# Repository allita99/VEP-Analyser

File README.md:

# VEP-Analyser-Motherboard

This repository contains an updated version of the hardware and software developed during my Bachelor's thesis, with incremental improvements and ongoing refinements.

The project integrates multiple components required for a VEP-based system, including firmware, sensor hardware, and the main motherboard design.

---

## Contents

* **Microcontroller Code**
  Firmware used for signal acquisition, control, and system interaction.

* **Motherboard Design**
  Central hardware platform responsible for system integration, power distribution, and communication between components.

* **VEP Sensor (VEPsor) Design**
  Hardware for acquiring visual evoked potential signals.

---

## Status

This repository reflects a working but evolving system:

* Several design and implementation improvements have been applied compared to the original thesis version
* Some components are still under development or require further validation
* Minor inconsistencies or unfinished elements may remain

---

## Purpose

The project is intended for:

* Research and experimentation in Brain-Computer Interfaces (BCI)
* Development and testing of VEP-based acquisition systems
* Educational use and hardware/software prototyping

---

## Notes

* Hardware designs may require verification before fabrication
* Firmware may need adaptation depending on the specific setup
* Some features are still work in progress and subject to change

---

Acknowledgement

Parts of the documentation and written content in this repository were generated with the assistance of AI tools. The text may be revised in the future if inaccuracies, inconsistencies, or improvements are identified.

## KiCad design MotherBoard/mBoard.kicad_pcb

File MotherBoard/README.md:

# VEPsor – Motherboard Hardware

The **VEPsor Motherboard** is the central hardware component of the VEP Analyzer project. It functions as the primary interface between VEP sensor modules, processing units, and external systems, enabling reliable data acquisition and seamless system integration.

This repository contains all resources required to review, manufacture, and assemble the motherboard.

---

## Preview

---

## Repository Contents

- **KiCad Project Files**  
  Complete schematic and PCB layout files for modification and extension.

- **Bill of Materials (BOM)**  
  Comprehensive list of components required for assembly.

- **Gerber Files**  
  Manufacturing-ready files for PCB fabrication.

- **schematics.pdf**  
  Exported schematic for quick inspection of the circuit design.

---

## Overview

The motherboard is designed to:

- Interface with VEP sensor modules  
- Provide stable power distribution across the system  
- Enable communication between hardware components  
- Serve as a reliable platform for BCI system integration  

### Key Design Goals

- Modular integration with sensor units  
- Robust signal routing and power management  
- Use of standard, widely available components  
- Expandability for future system extensions  

---

## Getting Started

### 1. Review the Design
- Open the KiCad project files for full access to the design  
- Use `schematics.pdf` for a quick overview  

### 2. PCB Fabrication
- Upload the Gerber files to a PCB manufacturer (e.g., JLCPCB, PCBWay)

### 3. Component Sourcing
- Use the BOM to procure all required components  

### 4. Assembly
- Assemble the board according to the PCB layout and schematic  
- Verify all power rails and connections before powering the system  

---

## Notes

- Ensure proper handling of power distribution sections  
- Follow ESD safety procedures during assembly  
- Validate voltage levels before connecting sensor modules  

---

## Intended Use

This hardware is intended for:

- Research and development in BCI systems  
- Integration of VEP-based sensing platforms  
- Experimental signal acquisition and processing setups  

This system is **not intended for medical or clinical use**.

---

## Feedback and Contributions

Feedback is encouraged. If you identify a bug, design issue, documentation error, or have suggestions for improvement, please open an Issue.

Constructive comments and contributions are welcome.

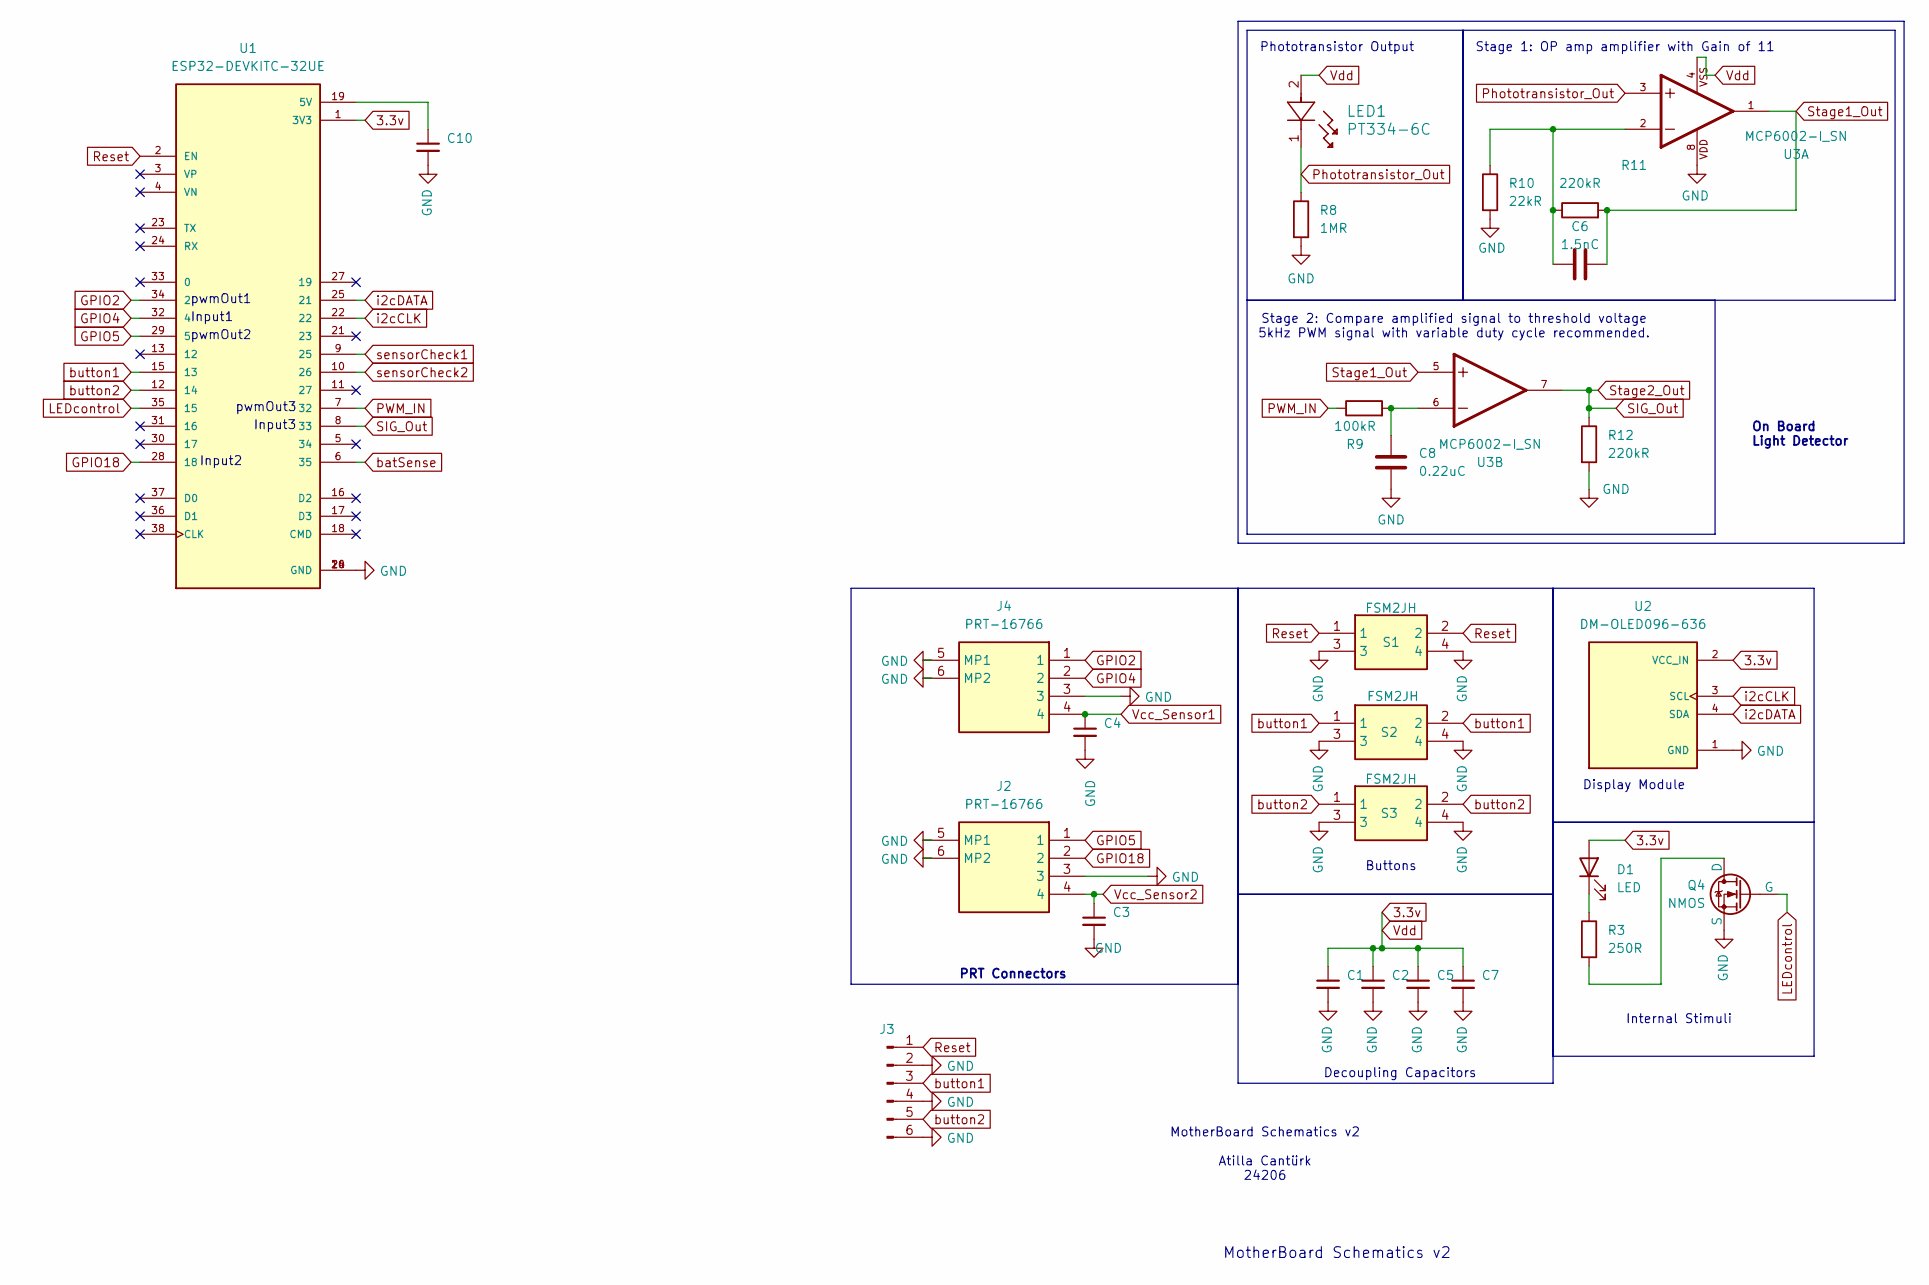
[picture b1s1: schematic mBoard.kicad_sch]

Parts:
C1, C2, C3, C4, C5, C7, C10: C_Small; C_1206_3216Metric_Pad1.33x1.80mm_HandSolder
C6: 1.5nC; C_1206_3216Metric_Pad1.33x1.80mm_HandSolder
C8: 0.22uC; C_1206_3216Metric_Pad1.33x1.80mm_HandSolder
D1: LED; LED_D5.0mm
J2, J4: PRT-16766; PRT16766; Mouser Part Number 474-PRT-16766
J3: Conn_01x06_Pin; PinHeader_1x06_P2.54mm_Vertical
LED1: PT334-6C; LED_D5.0mm
Q4: NMOS; SOT-23_Handsoldering
R3: 250R; R_1206_3216Metric_Pad1.30x1.75mm_HandSolder
R8: 1MR; R_1206_3216Metric_Pad1.30x1.75mm_HandSolder
R9: 100kR; R_1206_3216Metric_Pad1.30x1.75mm_HandSolder
R10: 22kR; R_1206_3216Metric_Pad1.30x1.75mm_HandSolder
R11, R12: 220kR; R_1206_3216Metric_Pad1.30x1.75mm_HandSolder
S1, S2, S3: FSM2JH; FSM4JH; Mouser Part Number 506-FSM2JH
U1: ESP32-DEVKITC-32UE; ESPRESSIF_ESP32-DEVKITC-32UE; PARTREV V4
U2: DM-OLED096-636; MODULE_DM-OLED096-636; PARTREV 2018-09-10
U3: MCP6002-I_SN; SOIC127P600X175-8N; PARTREV L

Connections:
3.3v: C1.1, C2.1, C5.1, C7.1, D1.2 (A), LED1.2, U1.1 (3V3), U2.2 (VCC_IN), U3.4
GND: C1.2, C2.2, C3.2, C4.2, C5.2, C7.2, C8.2, C10.2, J2.3, J2.5 (MP1), J2.6 (MP2), J3.2, J3.4, J3.6, J4.3, J4.5 (MP1), J4.6 (MP2), Q4.2 (S), R8.2, R10.2, R12.2, S1.3, S1.4, S2.3, S2.4, S3.3, S3.4, U1.14 (GND), U1.20 (GND), U1.26 (GND), U2.1 (GND), U3.8
GPIO2: J4.1, U1.34 (2)
GPIO4: J4.2, U1.32 (4)
GPIO5: J2.1, U1.29 (5)
GPIO18: J2.2, U1.28 (18)
LEDcontrol: Q4.1 (G), U1.35 (15)
unnamed: C6.1, R10.1, R11.1, U3.2
unnamed: C8.1, R9.2, U3.6
unnamed: D1.1 (K), R3.1
unnamed: Q4.3 (D), R3.2
unnamed: C10.1, U1.19 (5V)
PWM_IN: R9.1, U1.7 (32)
Phototransistor_Out: LED1.1, R8.1, U3.3
Reset: J3.1, S1.1, S1.2, U1.2 (EN)
SIG_Out: R12.1, U1.8 (33), U3.7
Stage1_Out: C6.2, R11.2, U3.1, U3.5
Vcc_Sensor1: C4.1, J4.4
Vcc_Sensor2: C3.1, J2.4
batSense: U1.6 (35)
button1: J3.3, S2.1, S2.2, U1.15 (13)
button2: J3.5, S3.1, S3.2, U1.12 (14)
i2cCLK: U1.22, U2.3 (SCL)
i2cDATA: U1.25 (21), U2.4 (SDA)
sensorCheck1: U1.9 (25)
sensorCheck2: U1.10 (26)

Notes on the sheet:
Input2
Phototransistor Output
Input1
Internal Stimuli
On Board Light Detector
pwmOut1
Display Module
Stage 2: Compare amplified signal to threshold voltage 5kHz PWM signal with variable duty cycle recommended.
pwmOut3
MotherBoard Schematics v2
Input3
Decoupling Capacitors
pwmOut2
MotherBoard Schematics v2 Atilla Cantürk 24206
Buttons
PRT Connectors
Stage 1: OP amp amplifier with Gain of 11

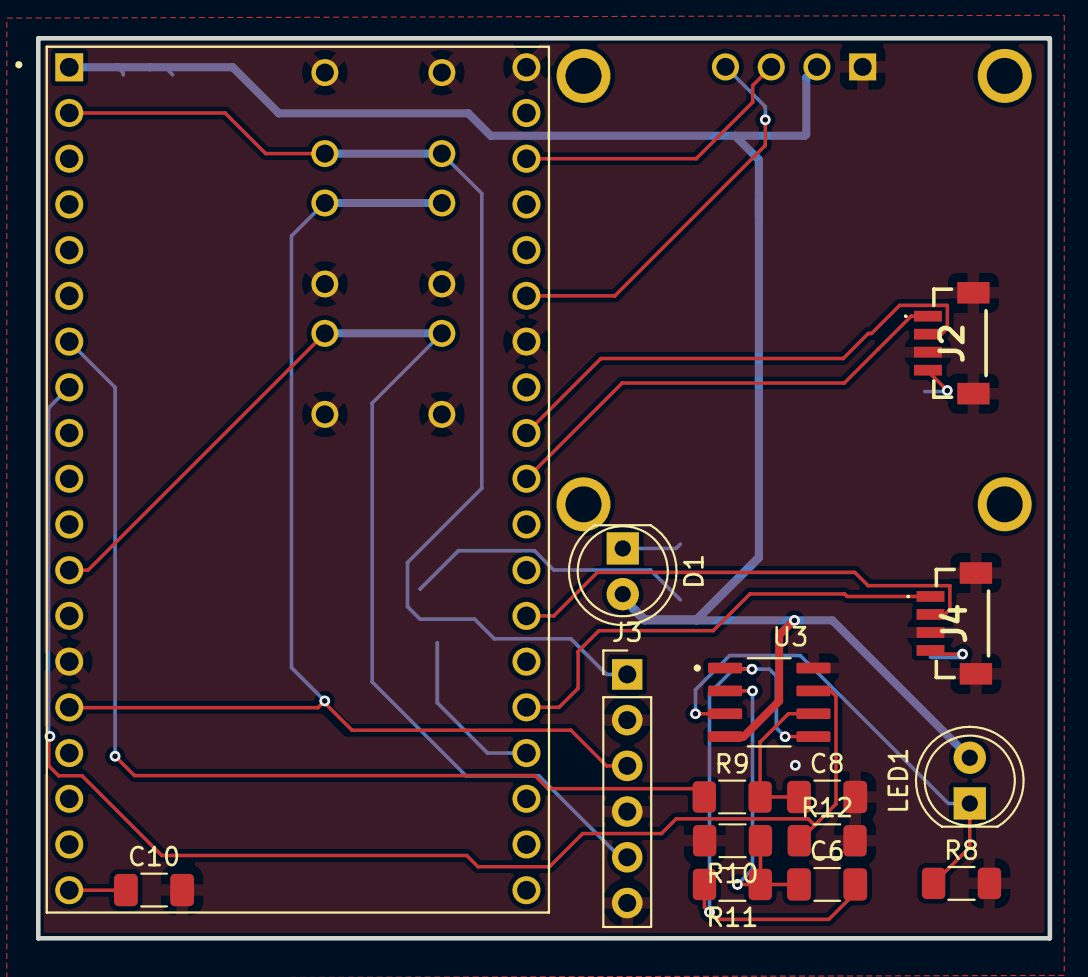
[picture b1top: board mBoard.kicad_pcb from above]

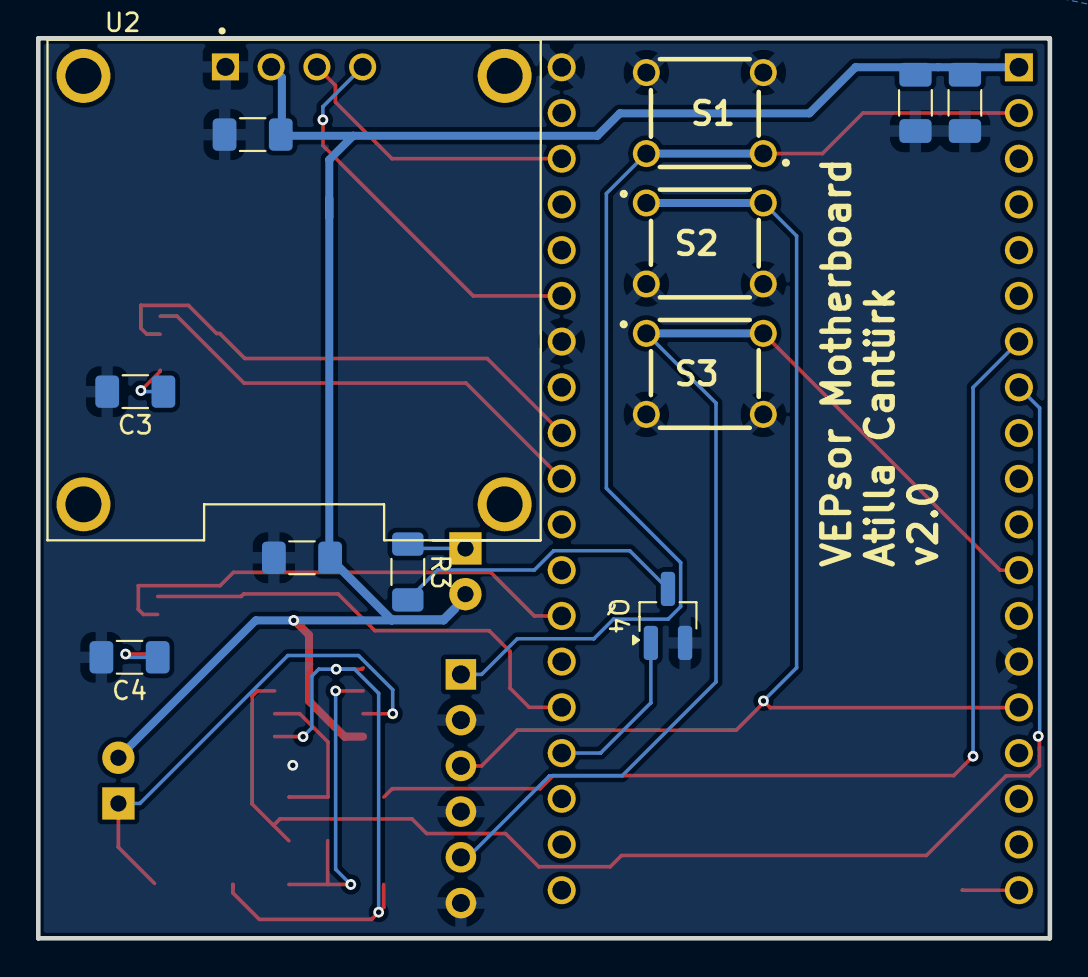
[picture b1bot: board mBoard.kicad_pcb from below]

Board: 2 copper layers, 56.2 x 50.0 mm, 27 parts (12 on the bottom side), 23 nets.

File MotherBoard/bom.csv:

Designator,Footprint,Quantity,Value,LCSC Part #
"C1, C10, C2, C3, C4, C5, C7",1206,7,C_Small,
C6,1206,1,1.5nC,
C8,1206,1,0.22uC,
D1,LED_D5.0mm,1,LED,
"J2, J4",PRT16766,2,PRT-16766,
J3,PinHeader_1x06_P2.54mm_Vertical,1,Conn_01x06_Pin,
LED1,LED_D5.0mm,1,PT334-6C,
Q4,SOT-23_Handsoldering,1,NMOS,
R10,1206,1,22kR,
"R11, R12",1206,2,220kR,
R3,1206,1,250R,
R8,1206,1,1MR,
R9,1206,1,100kR,
"S1, S2, S3",FSM4JH,3,FSM2JH,
U1,ESPRESSIF_ESP32-DEVKITC-32UE,1,ESP32-DEVKITC-32UE,
U2,MODULE_DM-OLED096-636,1,DM-OLED096-636,
U3,SOIC127P600X175-8N,1,MCP6002-I_SN,

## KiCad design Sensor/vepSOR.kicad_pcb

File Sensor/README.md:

# VEPsor – VEP Sensor Hardware

**VEPsor (VEP Sensor)** is the hardware acquisition component of the VEP Analyzer project. It provides a compact and reproducible platform for capturing visual evoked potentials (VEPs) in Brain-Computer Interface (BCI) applications.

This repository contains all resources required to review, manufacture, and assemble the hardware.

---

## Preview

---

## Repository Contents

- **KiCad Project Files**  
  Complete schematic and PCB design files for editing and modification.

- **Bill of Materials (BOM)**  
  Comprehensive list of components required for assembly.

- **Gerber Files**  
  Manufacturing-ready files for PCB fabrication.

- **schematics.pdf**  
  Exported schematic for quick inspection and validation of the circuit design.

---

## Overview

The VEPsor board is designed for:

- Acquisition of EEG signals related to visual stimuli  
- Integration into BCI systems  
- Rapid prototyping and experimental validation  

### Key Design Goals

- Reproducibility  
- Use of accessible, standard components  
- Compatibility with common EEG acquisition workflows  

---

## Getting Started

### 1. Review the Design
- Open the KiCad project files for full access to schematics and layout  
- Alternatively, inspect `schematics.pdf` for a quick overview  

### 2. PCB Fabrication
- Upload the Gerber files to a PCB manufacturer (e.g., JLCPCB, PCBWay)

### 3. Component Sourcing
- Use the BOM to order all required components  

### 4. Assembly
- Assemble the PCB according to the schematic and layout  
- Verify all connections before powering the board  

---

## Notes

- Handle analog and sensitive components with care  
- Follow ESD protection practices during assembly  
- Verify power supply requirements before operation  

---

## Intended Use

This hardware is intended for:

- Research and educational purposes  
- Experimental BCI systems  
- VEP signal acquisition and analysis  

This system is **not intended for medical or clinical use**.

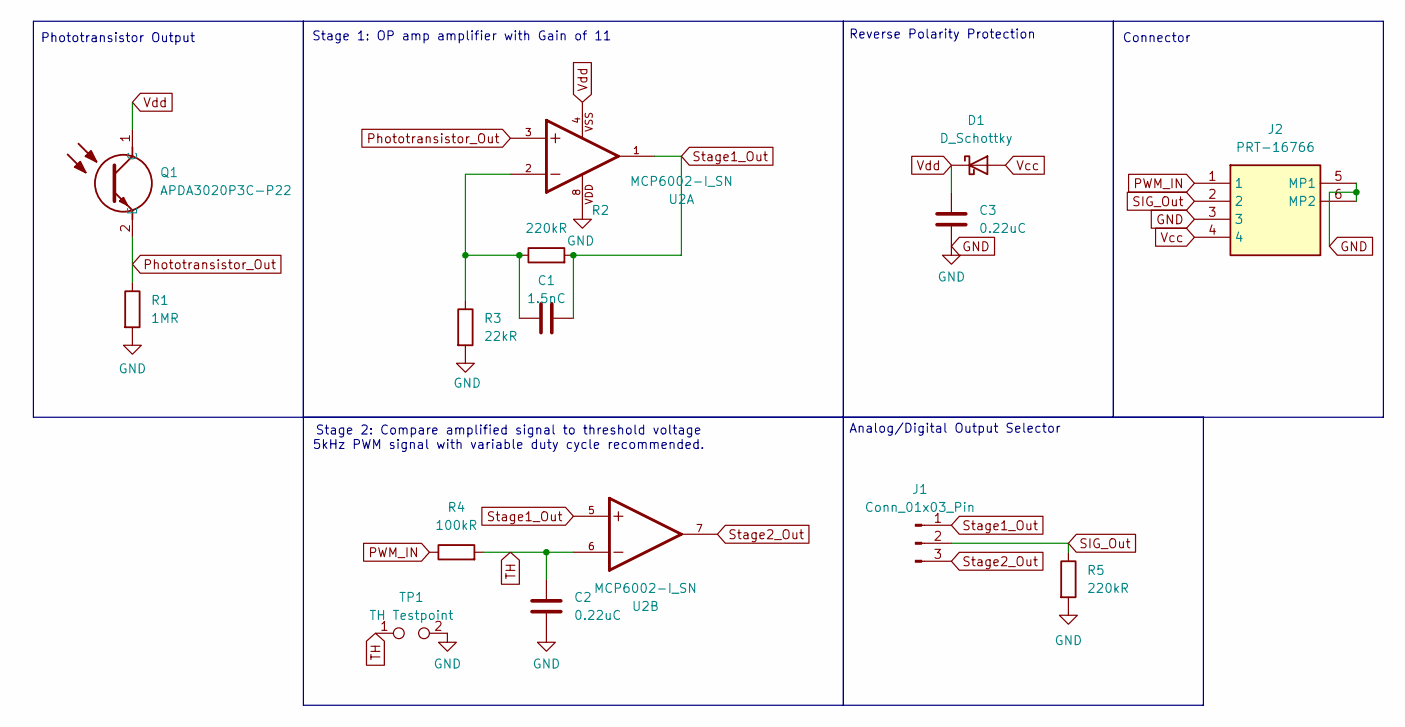
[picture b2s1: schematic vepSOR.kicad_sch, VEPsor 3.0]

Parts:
C1: 1.5nC; C_1206_3216Metric_Pad1.33x1.80mm_HandSolder
C2, C3: 0.22uC; C_1206_3216Metric_Pad1.33x1.80mm_HandSolder
D1: D_Schottky; SOD3716X135N
J1: Conn_01x03_Pin; SolderJumper-3_P1.3mm_Open_RoundedPad1.0x1.5mm_NumberLabels
J2: PRT-16766; PRT16766; Mouser Part Number 474-PRT-16766
Q1: APDA3020P3C-P22; APDA3020P3CP22; Manufacturer_Part_Number APDA3020P3C-P22
R1: 1MR; R_1206_3216Metric_Pad1.30x1.75mm_HandSolder
R2, R5: 220kR; R_1206_3216Metric_Pad1.30x1.75mm_HandSolder
R3: 22kR; R_1206_3216Metric_Pad1.30x1.75mm_HandSolder
R4: 100kR; R_1206_3216Metric_Pad1.30x1.75mm_HandSolder
TP1: TH Testpoint; TestPoint_Pad_1.0x1.0mm
U2: MCP6002-I_SN; SOIC127P600X175-8N; PARTREV L

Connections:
GND: C2.2, C3.2, J2.3, J2.5 (MP1), J2.6 (MP2), R1.2, R3.2, R5.2, TP1.2, U2.8
unnamed: C1.1, R2.1, R3.1, U2.2
PWM_IN: J2.1, R4.1
Phototransistor_Out: Q1.2 (E), R1.1, U2.3
SIG_Out: J1.2, J2.2, R5.1
Stage1_Out: C1.2, J1.1, R2.2, U2.1, U2.5
Stage2_Out: J1.3, U2.7
TH: C2.1, R4.2, TP1.1, U2.6
Vcc: D1.2 (A), J2.4
Vdd: C3.1, D1.1 (K), Q1.1 (C), U2.4

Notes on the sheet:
Reverse Polarity Protection
Analog/Digital Output Selector
Phototransistor Output
Stage 2: Compare amplified signal to threshold voltage 5kHz PWM signal with variable duty cycle recommended.
Connector
Stage 1: OP amp amplifier with Gain of 11

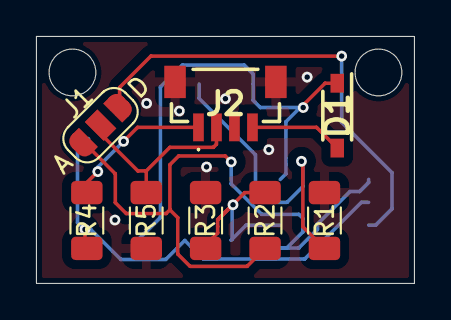
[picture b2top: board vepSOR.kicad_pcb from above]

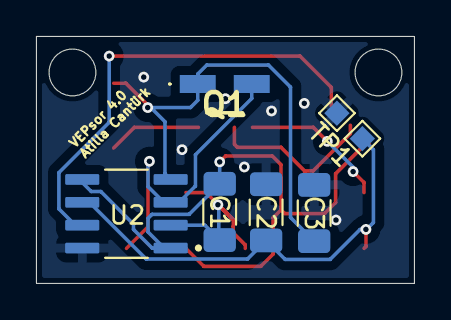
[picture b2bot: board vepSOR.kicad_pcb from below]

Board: 2 copper layers, 21.0 x 13.7 mm, 14 parts (6 on the bottom side), 10 nets.

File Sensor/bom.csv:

Designator,Footprint,Quantity,Value,LCSC Part #
C1,1206,1,1.5nC,
"C2, C3",1206,2,0.22uC,
D1,SOD3716X135N,1,D_Schottky,
J1,SolderJumper-3_P1.3mm_Open_RoundedPad1.0x1.5mm_NumberLabels,1,Conn_01x03_Pin,
J2,PRT16766,1,PRT-16766,
Q1,APDA3020P3CP22,1,APDA3020P3C-P22,
R1,1206,1,1MR,
"R2, R5",1206,2,220kR,
R3,1206,1,22kR,
R4,1206,1,100kR,
TP1,TestPoint_Pad_1.0x1.0mm,1,TH Testpoint,
U2,SOIC127P600X175-8N,1,MCP6002-I_SN,

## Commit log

2026-04-03 Initial Push
2026-04-03 .md fixes
2026-04-03 .md fix
